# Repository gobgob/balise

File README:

CODE TO TRY LOGIC FILTER WITH FFT

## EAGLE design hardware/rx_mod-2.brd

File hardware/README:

Un premier recepteur (rx.sch et rx.brd) que j'ai raté à la fabrication. De plus, la masse virtuel oscille à 5kHz environ avec une amplitude de 1V.

Fabrication d'un autre récepteur en 2 modules : 
	* Module 1 : Le décodage du signal (ampli et filtre simple) pour 2 voies avec masse virtuel sur suiveur d'un AO.
	* Module 2 : Carte micro pour un ATmega328p (que l'on peut remplacer par un arduino si on veut).

Emetteur qui controle les LED avec un microcontroleur.

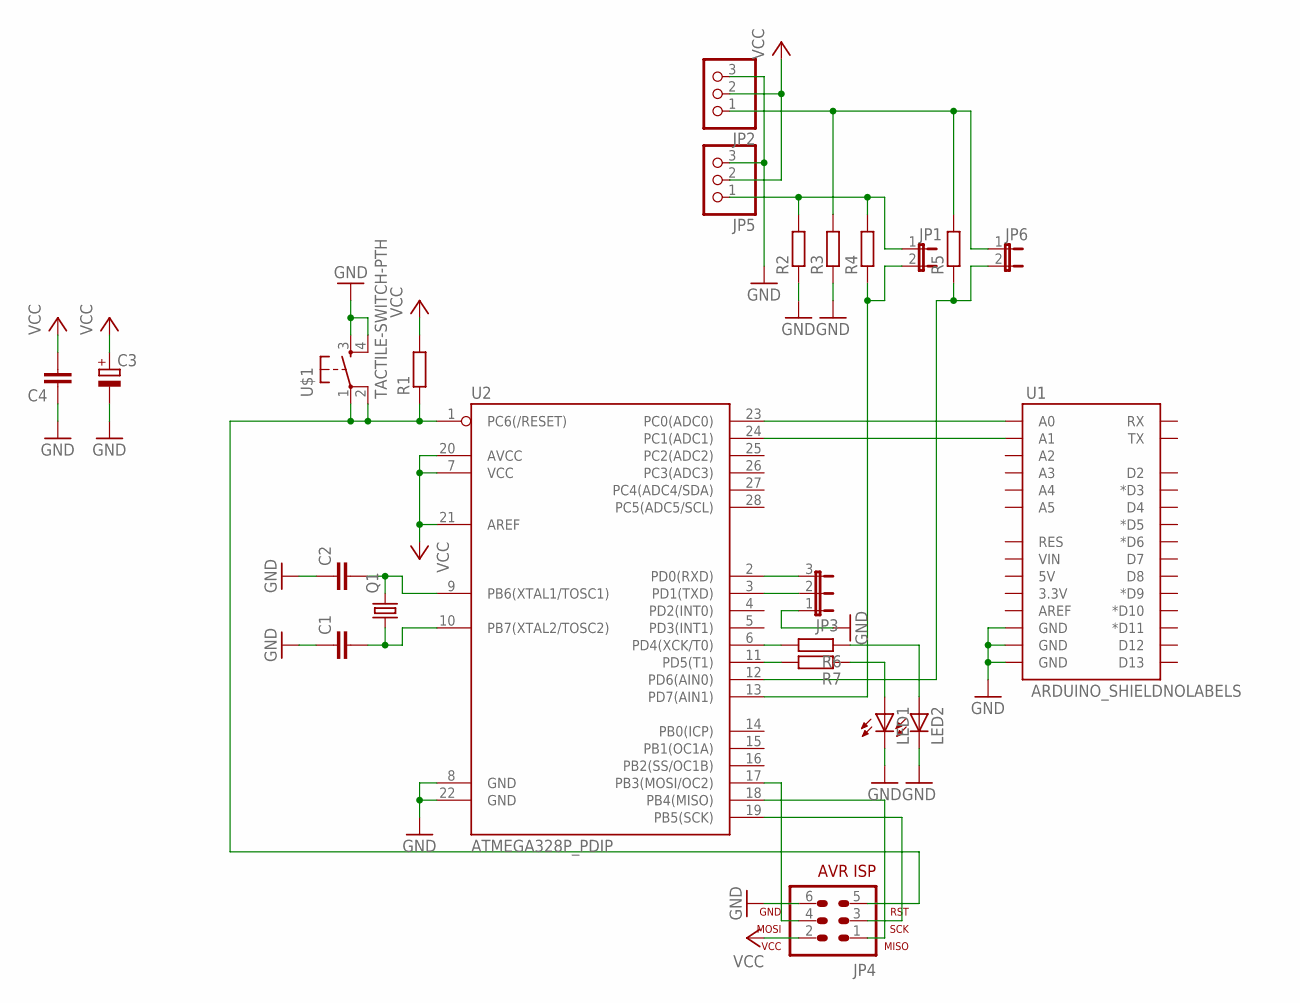
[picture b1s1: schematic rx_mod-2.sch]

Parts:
C1, C2, C4: C-EU050-030X075; C050-030X075
C3: CPOL-EUE2.5-6; E2,5-6
JP1, JP6: JP1E; JP1
JP2, JP5: PINHD-1X3/90; 1X03/90
JP3: JP2E; JP2
JP4: AVR-ISP-6VERT; AVR-ISP-6
LED1, LED2: LED5MM
Q1: CRYSTALHC49U70; HC49U70
R1, R2, R3, R4, R5, R6, R7: R-EU_0207/10; 0207/10
U1: ARDUINO_SHIELDNOLABELS; DUEMILANOVE_SHIELD_NOLABELS
U2: ATMEGA328P_PDIP; DIL28-3
U$1: TACTILE-SWITCH-PTH; TAC-SWITCH-PTH

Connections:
GND: C1.1, C2.1, C3.-, C4.1, JP2.3, JP3.1, JP4.6, JP5.3, LED1.K (C), LED2.K (C), R2.1, R3.1, U1.GND@0 (GND), U1.GND@1 (GND), U1.GND@2 (GND), U2.8 (GND), U2.22 (GND), U$1.3, U$1.4
unnamed: JP6.2, R5.1, U2.12 (PD6(AIN0))
unnamed: JP1.2, R4.1, U2.13 (PD7(AIN1))
unnamed: JP1.1, JP5.1, R2.2, R4.2
unnamed: JP2.1, JP6.1, R3.2, R5.2
unnamed: JP4.5, R1.1, U2.1 (PC6(/RESET)), U$1.1, U$1.2
unnamed: JP3.2, U2.3 (PD1(TXD))
unnamed: JP3.3, U2.2 (PD0(RXD))
unnamed: C2.2, Q1.2, U2.9 (PB6(XTAL1/TOSC1))
unnamed: C1.2, Q1.1, U2.10 (PB7(XTAL2/TOSC2))
unnamed: JP4.4, U2.17 (PB3(MOSI/OC2))
unnamed: JP4.1, U2.18 (PB4(MISO))
unnamed: JP4.3, U2.19 (PB5(SCK))
unnamed: R7.2, U2.11 (PD5(T1))
unnamed: R6.2, U2.6 (PD4(XCK/T0))
unnamed: LED2.A, R6.1
unnamed: LED1.A, R7.1
unnamed: U1.A0, U2.23 (PC0(ADC0))
unnamed: U1.A1, U2.24 (PC1(ADC1))
VCC: C3.+, C4.2, JP2.2, JP4.2, JP5.2, R1.2, U2.7 (VCC), U2.20 (AVCC), U2.21 (AREF)

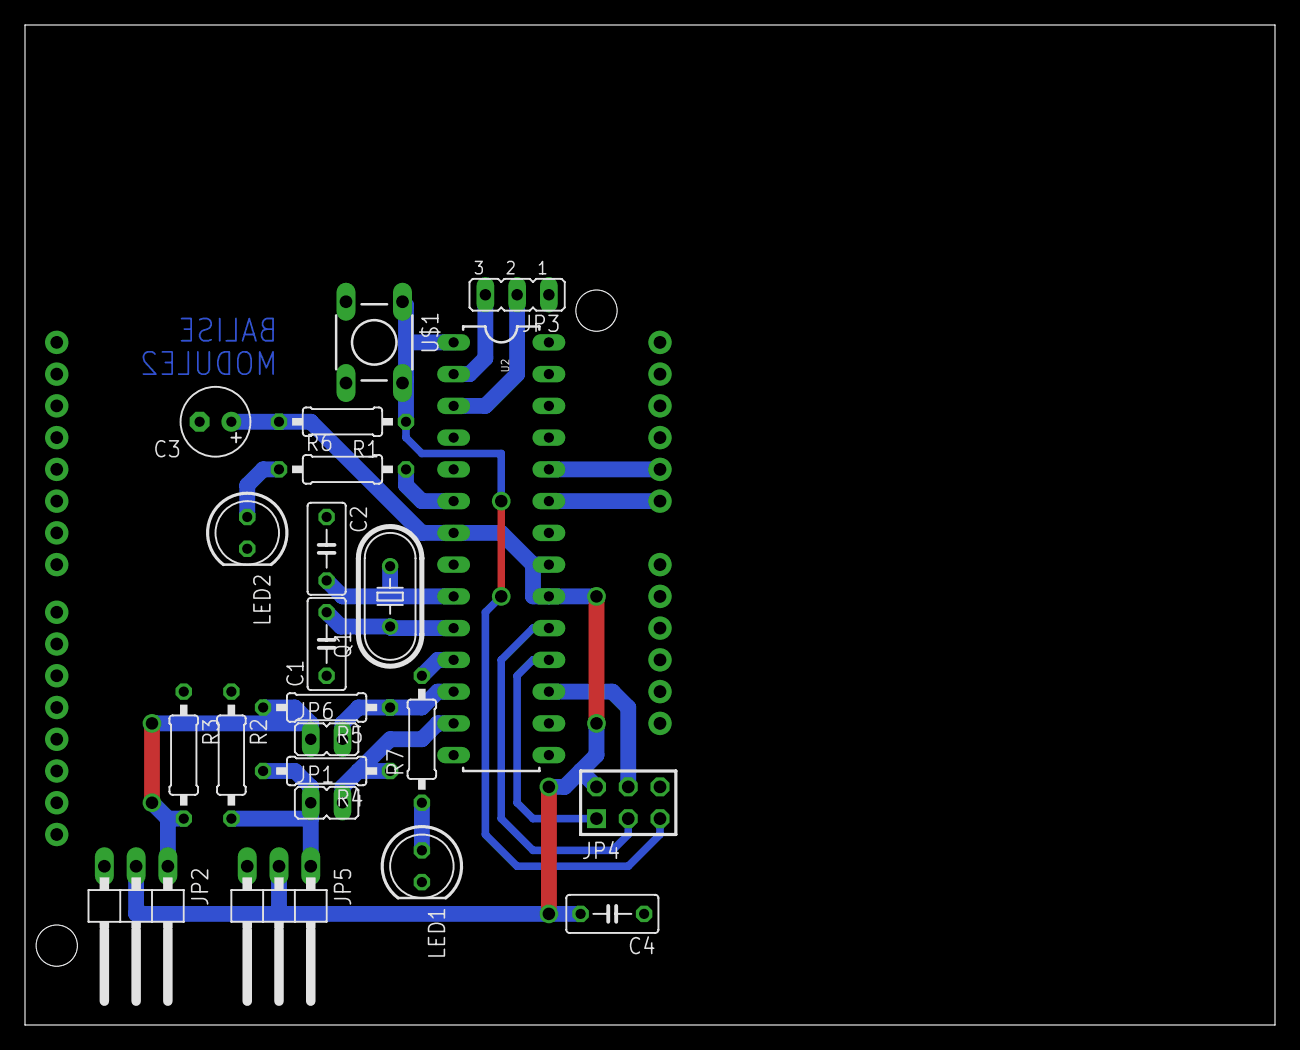
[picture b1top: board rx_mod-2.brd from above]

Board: 2 copper layers, 100.0 x 80.0 mm, 23 parts (0 on the bottom side), 20 nets.

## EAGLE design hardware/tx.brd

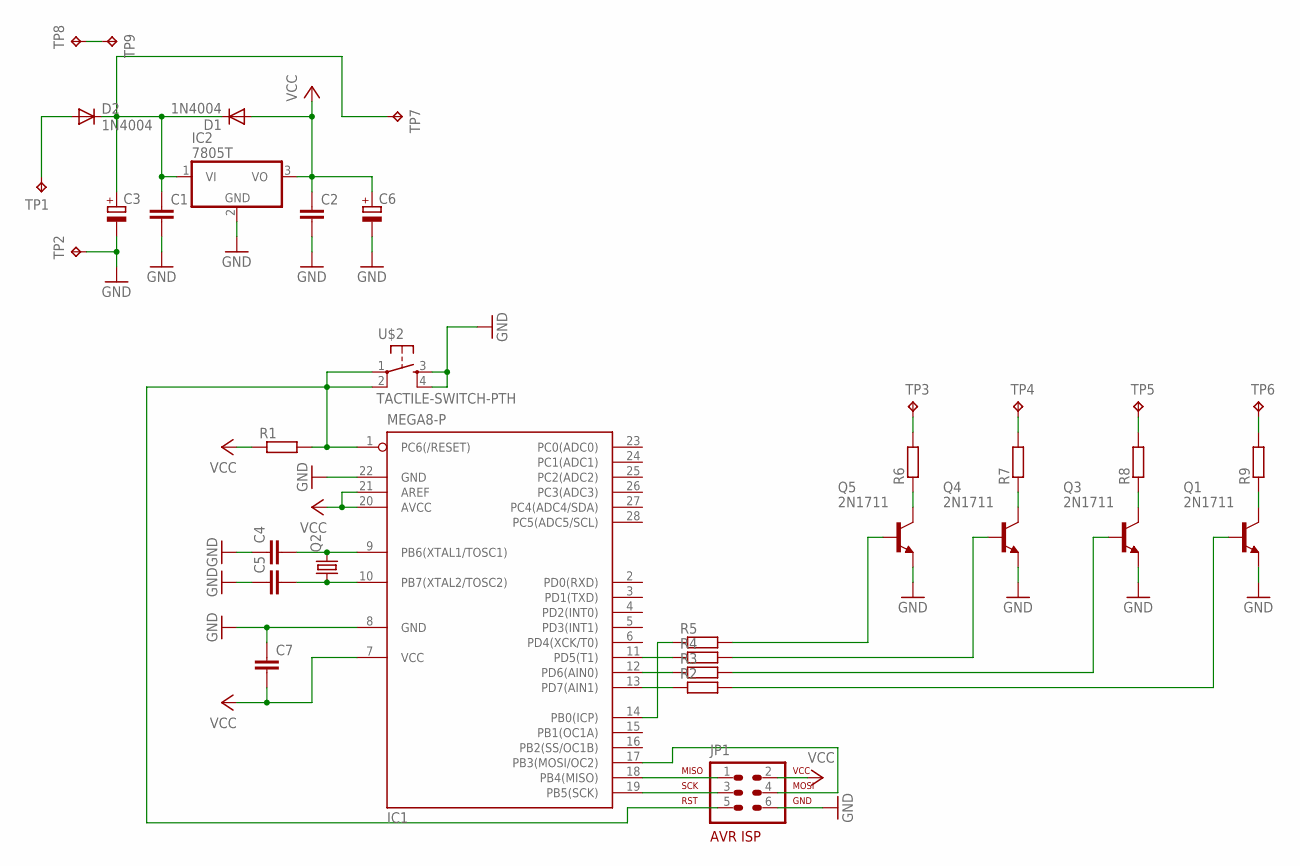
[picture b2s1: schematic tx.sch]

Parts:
C1, C2, C4, C5, C7: C-EU050-030X075; C050-030X075
C3, C6: CPOL-EUE3.5-8; E3,5-8
D1, D2: 1N4004; DO41-10
IC1: MEGA8-P; DIL28-3
IC2: 7805T; TO220H
JP1: AVR-ISP-6HORZ; AVR-ISP-6R
Q1, Q3, Q4, Q5: 2N1711; TO39
Q2: CRYSTALHC49U70; HC49U70
R1, R2, R3, R4, R5, R6, R7, R8, R9: R-EU_0204/7; 0204/7
TP1, TP2, TP3, TP4, TP5, TP6, TP7, TP8, TP9: TPPAD1-13Y; P1-13Y
U$2: TACTILE-SWITCH-PTH; TAC-SWITCH-PTH

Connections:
GND: C1.2, C2.2, C3.-, C4.1, C5.1, C6.-, C7.1, IC1.8 (GND), IC1.22 (GND), IC2.2 (GND), JP1.6, Q1.1 (E), Q3.1 (E), Q4.1 (E), Q5.1 (E), TP2.TP, U$2.3, U$2.4
unnamed: TP8.TP, TP9.TP
unnamed: C1.1, C3.+, D1.C, D2.C, IC2.1 (VI), TP7.TP
unnamed: IC1.1 (PC6(/RESET)), JP1.5, R1.2, U$2.1, U$2.2
unnamed: IC1.18 (PB4(MISO)), JP1.1
unnamed: IC1.19 (PB5(SCK)), JP1.3
unnamed: IC1.17 (PB3(MOSI/OC2)), JP1.4
unnamed: IC1.14 (PB0(ICP)), R5.1
unnamed: C4.2, IC1.9 (PB6(XTAL1/TOSC1)), Q2.2
unnamed: C5.2, IC1.10 (PB7(XTAL2/TOSC2)), Q2.1
unnamed: D2.A, TP1.TP
unnamed: IC1.11 (PD5(T1)), R4.1
unnamed: IC1.12 (PD6(AIN0)), R3.1
unnamed: IC1.13 (PD7(AIN1)), R2.1
unnamed: R6.2, TP3.TP
unnamed: R7.2, TP4.TP
unnamed: R8.2, TP5.TP
unnamed: R9.2, TP6.TP
unnamed: Q1.3 (C), R9.1
unnamed: Q3.3 (C), R8.1
unnamed: Q4.3 (C), R7.1
unnamed: Q5.3 (C), R6.1
unnamed: Q1.2 (B), R2.2
unnamed: Q3.2 (B), R3.2
unnamed: Q4.2 (B), R4.2
unnamed: Q5.2 (B), R5.2
VCC: C2.1, C6.+, C7.2, D1.A, IC1.7 (VCC), IC1.20 (AVCC), IC1.21 (AREF), IC2.3 (VO), JP1.2, R1.1

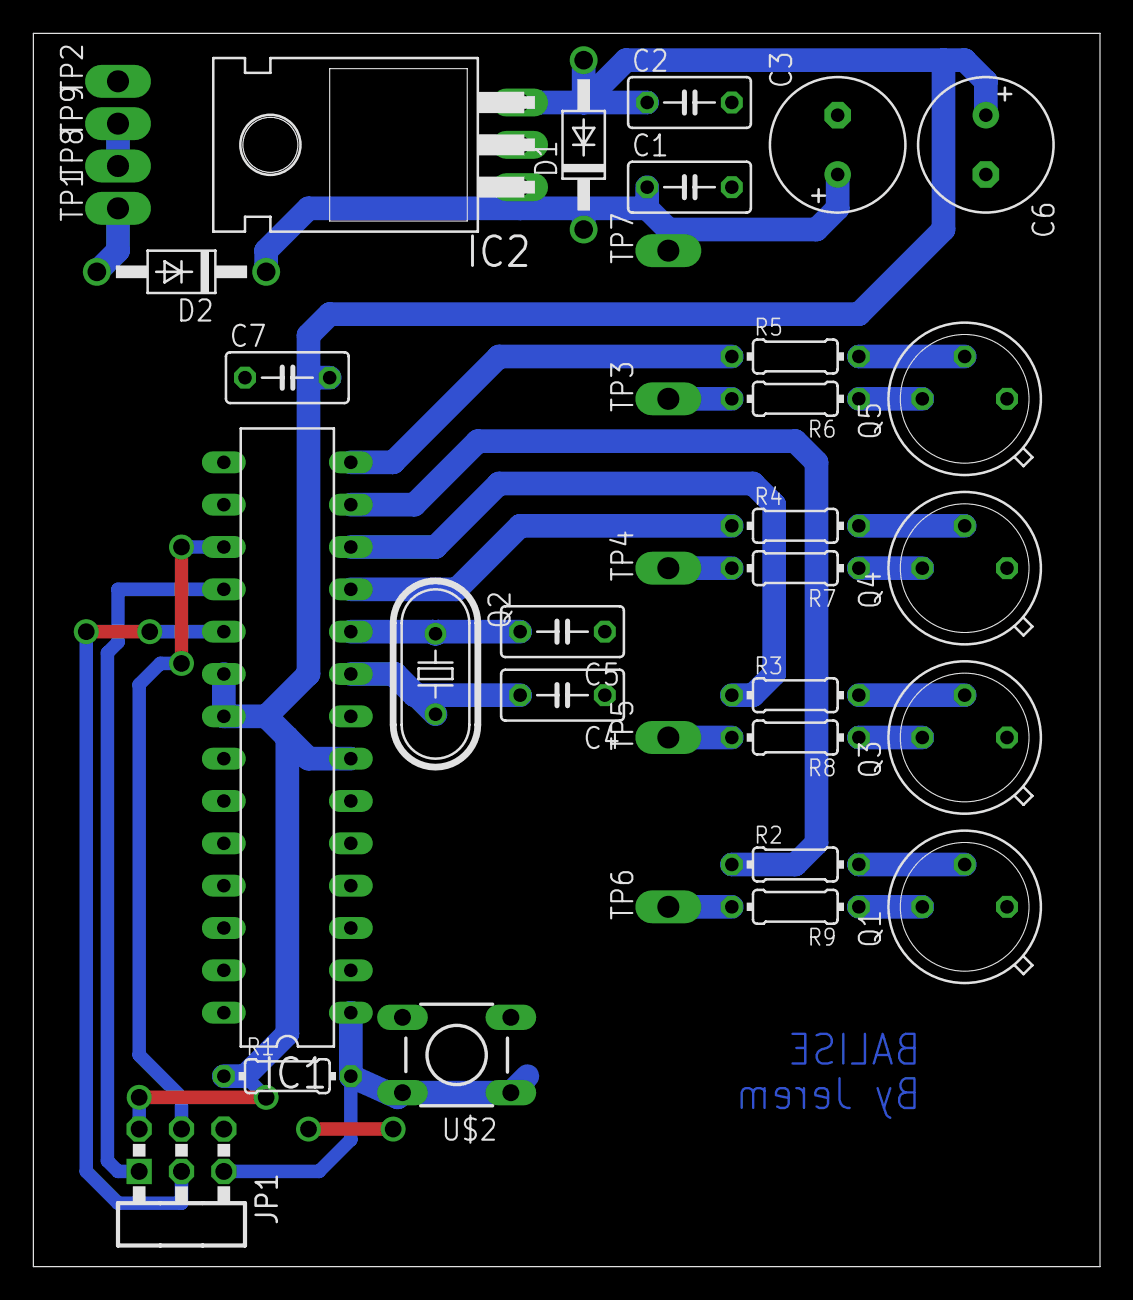
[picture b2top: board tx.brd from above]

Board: 2 copper layers, 64.0 x 74.0 mm, 36 parts (0 on the bottom side), 27 nets.

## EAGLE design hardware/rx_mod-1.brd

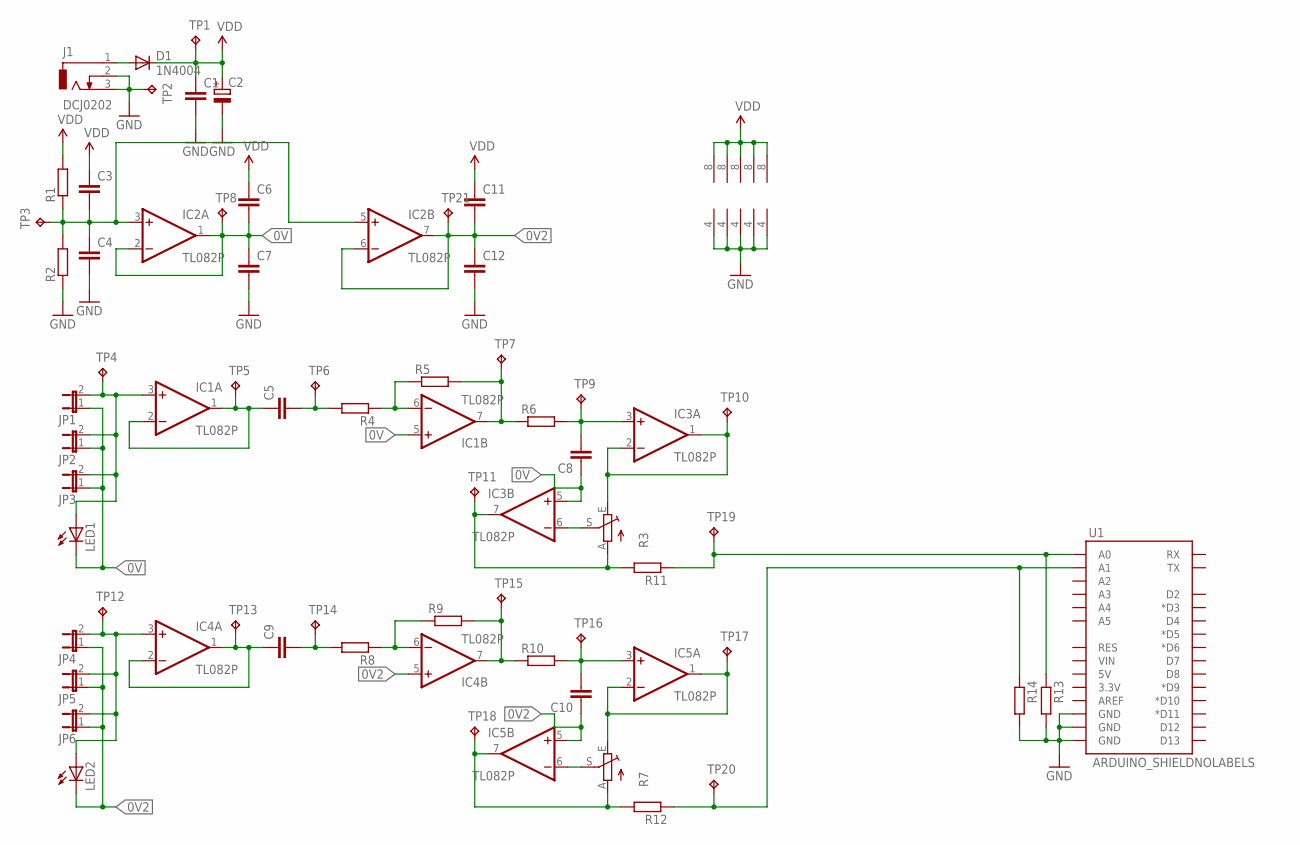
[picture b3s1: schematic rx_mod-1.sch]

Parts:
C1, C3, C4, C5, C6, C7, C8, C9, C10, C11, C12: C-EU050-030X075; C050-030X075
C2: CPOL-EUE2.5-6; E2,5-6
D1: 1N4004; DO41-10
IC1, IC2, IC3, IC4, IC5: TL082P; DIL08
J1: DCJ0202
JP1, JP2, JP3, JP4, JP5, JP6: JP1E; JP1
LED1, LED2: LED5MM
R1, R2, R4, R8, R11, R12, R13, R14: R-EU_0207/10; 0207/10
R3, R7: TRIM_EU-CA9V; CA9V
R5, R6, R9, R10: R-EU_0207/2V; 0207/2V
TP1, TP2, TP3, TP4, TP5, TP6, TP7, TP8, TP9, TP10, TP11, TP12, TP13, TP14, TP15, TP16, TP17, TP18, TP19, TP20, TP21: TPPAD1-13; P1-13
U1: ARDUINO_SHIELDNOLABELS; DUEMILANOVE_SHIELD_NOLABELS

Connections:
0V: C6.2, C7.1, C8.1, IC1.5 (+IN), IC2.1 (OUT), IC2.2 (-IN), IC3.5 (+IN), JP1.1, JP2.1, JP3.1, LED1.K (C), TP8.TP
0V2: C10.1, C11.2, C12.1, IC2.6 (-IN), IC2.7 (OUT), IC4.5 (+IN), IC5.5 (+IN), JP4.1, JP5.1, JP6.1, LED2.K (C), TP21.TP
GND: C1.2, C2.-, C4.2, C7.2, C12.2, IC1.4 (V-), IC2.4 (V-), IC3.4 (V-), IC4.4 (V-), IC5.4 (V-), J1.2, J1.3, R2.1, R13.2, R14.2, TP2.TP, U1.GND@0 (GND), U1.GND@1 (GND), U1.GND@2 (GND)
unnamed: D1.A, J1.1
unnamed: C5.1, IC1.1 (OUT), IC1.2 (-IN), TP5.TP
unnamed: IC1.3 (+IN), JP1.2, JP2.2, JP3.2, LED1.A, TP4.TP
unnamed: C5.2, R4.2, TP6.TP
unnamed: IC1.6 (-IN), R4.1, R5.1
unnamed: IC1.7 (OUT), R5.2, R6.1, TP7.TP
unnamed: C8.2, IC3.3 (+IN), R6.2, TP9.TP
unnamed: C3.2, C4.1, IC2.3 (+IN), IC2.5 (+IN), R1.1, R2.2, TP3.TP
unnamed: IC3.1 (OUT), IC3.2 (-IN), R3.E, TP10.TP
unnamed: IC4.3 (+IN), JP4.2, JP5.2, JP6.2, LED2.A, TP12.TP
unnamed: IC3.6 (-IN), R3.S
unnamed: IC3.7 (OUT), R3.A, R11.2, TP11.TP
unnamed: C9.1, IC4.1 (OUT), IC4.2 (-IN), TP13.TP
unnamed: C9.2, R8.2, TP14.TP
unnamed: IC4.6 (-IN), R8.1, R9.1
unnamed: IC4.7 (OUT), R9.2, R10.1, TP15.TP
unnamed: C10.2, IC5.3 (+IN), R10.2, TP16.TP
unnamed: IC5.1 (OUT), IC5.2 (-IN), R7.E, TP17.TP
unnamed: IC5.6 (-IN), R7.S
unnamed: IC5.7 (OUT), R7.A, R12.2, TP18.TP
unnamed: R11.1, R13.1, TP19.TP, U1.A0
unnamed: R12.1, R14.1, TP20.TP, U1.A1
VDD: C1.1, C2.+, C3.1, C6.1, C11.1, D1.C, IC1.8 (V+), IC2.8 (V+), IC3.8 (V+), IC4.8 (V+), IC5.8 (V+), R1.2, TP1.TP

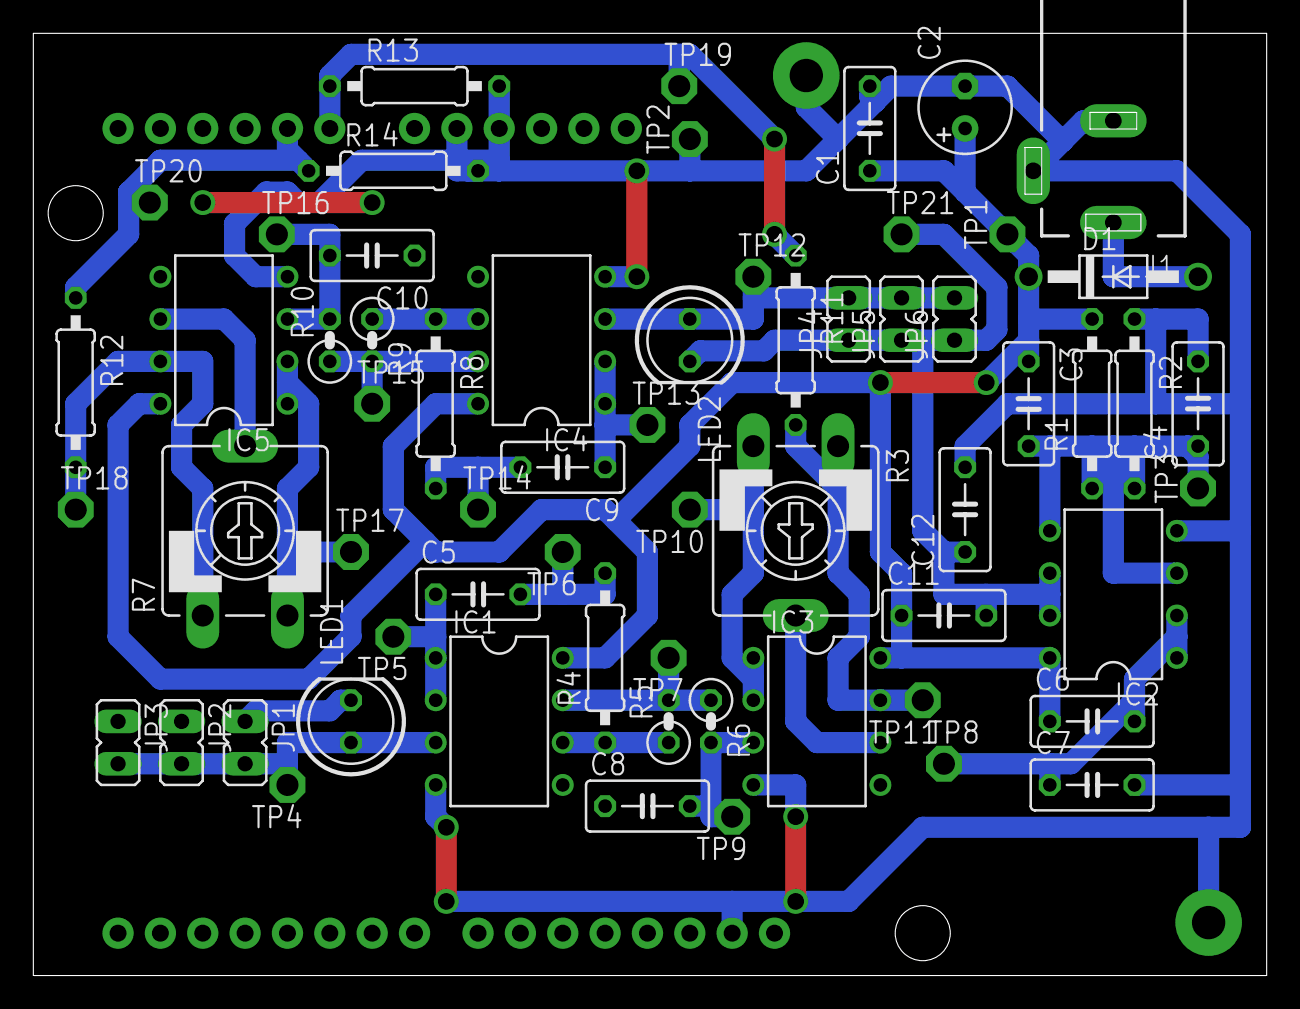
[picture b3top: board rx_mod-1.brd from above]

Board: 2 copper layers, 74.0 x 56.5 mm, 63 parts (0 on the bottom side), 26 nets.

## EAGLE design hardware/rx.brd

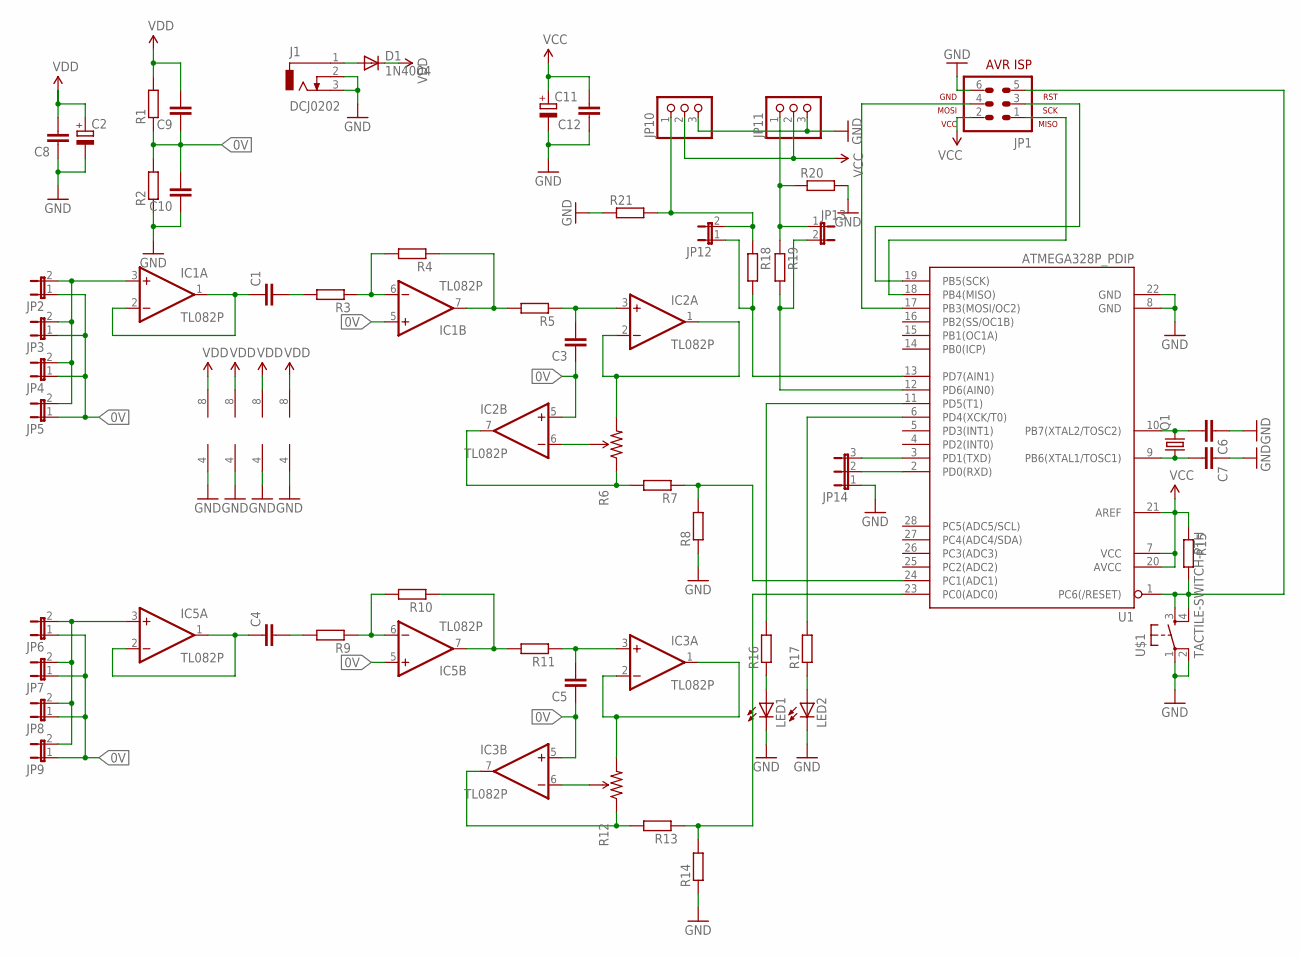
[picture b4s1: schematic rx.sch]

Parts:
C1, C3, C4, C5, C6, C7, C8, C9, C10, C12: C-EU050-030X075; C050-030X075
C2, C11: CPOL-EUE5-8.5; E5-8,5
D1: 1N4004; DO41-10
IC1, IC2, IC3, IC5: TL082P; DIL08
J1: DCJ0202
JP1: AVR-ISP-6VERT; AVR-ISP-6
JP2, JP3, JP4, JP5, JP6, JP7, JP8, JP9, JP12, JP13: JP1E; JP1
JP10, JP11: PINHD-1X3/90; 1X03/90
JP14: JP2E; JP2
LED1, LED2: LED5MM
Q1: CRYSTALHC49U70; HC49U70
R1, R2, R3, R7, R8, R9, R13, R14, R15, R16, R17, R18, R19, R20, R21: R-EU_0207/10; 0207/10
R4, R5, R10, R11: R-EU_0207/2V; 0207/2V
R6, R12: TRIMPOTPTH; TRIM_POT_PTH
U1: ATMEGA328P_PDIP; DIL28-3
U$1: TACTILE-SWITCH-PTH; TAC-SWITCH-PTH

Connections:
0V: C3.1, C5.1, C9.1, C10.2, IC1.5 (+IN), IC2.5 (+IN), IC3.5 (+IN), IC5.5 (+IN), JP2.1, JP3.1, JP4.1, JP5.1, JP6.1, JP7.1, JP8.1, JP9.1, R1.1, R2.2
GND: C2.-, C6.1, C7.1, C8.1, C10.1, C11.-, C12.1, IC1.4 (V-), IC2.4 (V-), IC3.4 (V-), IC5.4 (V-), J1.2, J1.3, JP1.6, JP10.3, JP11.3, JP14.1, LED1.K (C), LED2.K (C), R2.1, R8.1, R14.1, R20.2, R21.1, U1.8 (GND), U1.22 (GND), U$1.1, U$1.2
unnamed: C1.1, IC1.1 (OUT), IC1.2 (-IN)
unnamed: IC1.3 (+IN), JP2.2, JP3.2, JP4.2, JP5.2
unnamed: C1.2, R3.2
unnamed: IC1.6 (-IN), R3.1, R4.2
unnamed: IC1.7 (OUT), R4.1, R5.2
unnamed: IC2.1 (OUT), IC2.2 (-IN), R6.3 (CW)
unnamed: C3.2, IC2.3 (+IN), R5.1
unnamed: D1.A, J1.1
unnamed: IC2.6 (-IN), R6.2 (WIPER)
unnamed: IC2.7 (OUT), R6.1 (CCW), R7.2
unnamed: R7.1, R8.2, U1.24 (PC1(ADC1))
unnamed: IC5.3 (+IN), JP6.2, JP7.2, JP8.2, JP9.2
unnamed: C4.1, IC5.1 (OUT), IC5.2 (-IN)
unnamed: C4.2, R9.2
unnamed: IC5.6 (-IN), R9.1, R10.2
unnamed: IC5.7 (OUT), R10.1, R11.2
unnamed: IC3.1 (OUT), IC3.2 (-IN), R12.3 (CW)
unnamed: C5.2, IC3.3 (+IN), R11.1
unnamed: IC3.6 (-IN), R12.2 (WIPER)
unnamed: IC3.7 (OUT), R12.1 (CCW), R13.2
unnamed: R13.1, R14.2, U1.23 (PC0(ADC0))
unnamed: JP11.1, JP13.1, R19.1, R20.1
unnamed: C7.2, Q1.1, U1.9 (PB6(XTAL1/TOSC1))
unnamed: C6.2, Q1.2, U1.10 (PB7(XTAL2/TOSC2))
unnamed: JP10.1, JP12.2, R18.1, R21.2
unnamed: JP14.3, U1.3 (PD1(TXD))
unnamed: JP14.2, U1.2 (PD0(RXD))
unnamed: JP1.5, R15.2, U1.1 (PC6(/RESET)), U$1.3, U$1.4
unnamed: JP1.1, U1.18 (PB4(MISO))
unnamed: JP1.3, U1.19 (PB5(SCK))
unnamed: JP1.4, U1.17 (PB3(MOSI/OC2))
unnamed: LED1.A, R16.1
unnamed: LED2.A, R17.1
unnamed: R17.2, U1.6 (PD4(XCK/T0))
unnamed: R16.2, U1.11 (PD5(T1))
unnamed: JP13.2, R19.2, U1.12 (PD6(AIN0))
unnamed: JP12.1, R18.2, U1.13 (PD7(AIN1))
VCC: C11.+, C12.2, JP1.2, JP10.2, JP11.2, R15.1, U1.7 (VCC), U1.20 (AVCC), U1.21 (AREF)
VDD: C2.+, C8.2, C9.2, D1.C, IC1.8 (V+), IC2.8 (V+), IC3.8 (V+), IC5.8 (V+), R1.2

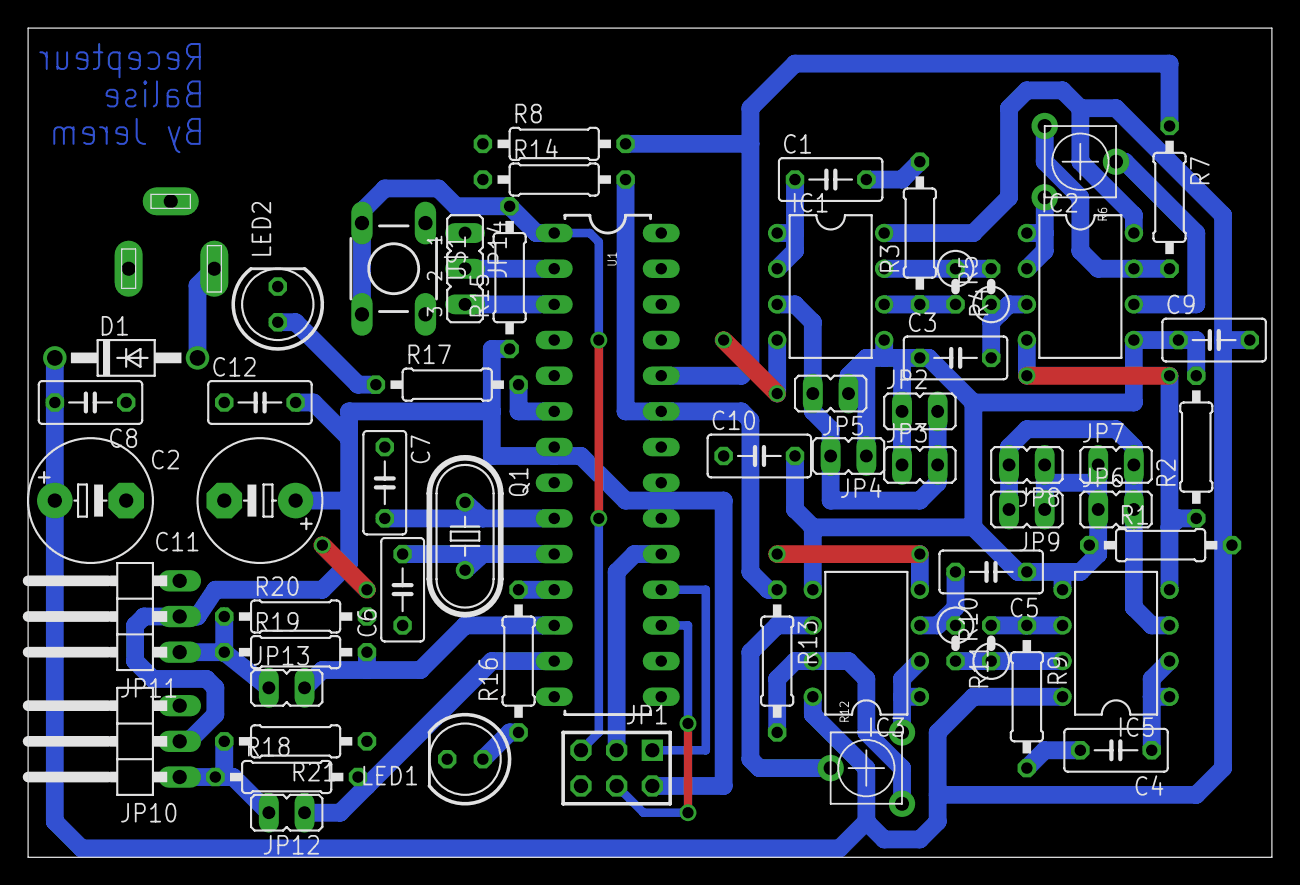
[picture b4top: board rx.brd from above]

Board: 2 copper layers, 88.6 x 59.0 mm, 58 parts (1 on the bottom side), 41 nets.

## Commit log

2014-05-25 Add gitignore
2014-05-25 Add global.h
2014-05-25 Add timer 0
2014-05-25 Add iox
2014-05-25 Add adc
2014-05-25 Add main filex
2014-05-25 Add Makefile
2014-05-25 Add fft file
2014-05-25 Change TIMER 0 OVF (with prescaler)
2014-05-25 Display time to compute fft
2014-05-25 Add function to Compute One argument of FFT
2014-05-25 Update Main.c : use Compute fft function
2014-05-26 Add uart for debug : implementation isn't finish
2014-05-26 update ADC convert
2014-05-26 update fft : give coef to compute fft
2014-05-26 add ISR for useless interrupt (just in case)
2014-05-26 Add uart in Makefile
2014-05-26 Main prog which compute fft for signal :)
2014-05-26 Create code to check presence of one frequency
2014-05-26 FFT compute with avr
2014-05-26 add exploit result on excel
2014-05-26 update exploited result
2014-05-27 Add sin and cos table to optimize speed
2014-05-27 Use sin and cos table whereas compute it
2015-05-18 Update Makefile
2015-05-18 Add ability to choose ADC
2015-05-18 Change fft compute : delete sqrt (to optimize speed)
2015-05-18 Add comment and new value for fft (but use the same as prev)
2015-05-18 Add other LED debug (like on schematic)
2015-05-18 Update main to check on the 2 side of robot
    And send value on uart
2015-05-18 Set receiver in folder receiver
2015-05-18 Add Transmitter source code
2015-05-18 Add Hardware schematic and board for balise
2015-05-18 Add solidworks file to print balise
2024-05-16 fix bug in makefile
2024-05-16 add option to compile with meson and ninja
2024-05-16 add Dockerfile to build the application
2024-05-16 restructure code and organisation
2024-05-16 use docker to compile transmitter and add ability to use meson instead of makefile

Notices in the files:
parts and their libraries:
SparkFun-Electromechanical: Licensing: Creative Commons ShareAlike 4.0 International - https://creativecommons.org/licenses/by-sa/4.0
